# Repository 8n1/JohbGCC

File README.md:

# JohbGCC v1.3

This board is based on the PhobGCC v1.2.3 board (https://github.com/PhobGCC/PhobGCC-HW).  
  
It is 100% compatible with the PhobGCC software but requires a custom teensy.h. (More info below).  

--- 
  
The Board was made with KiCad version 6.0.5.  
Gerber and assembly production files were created using the KiCad plugin "JLCPCB Tools"  (https://github.com/Bouni/kicad-jlcpcb-tools).  

# Changes

- **Rotated the stickbox into original position**  
- **Rotated the Teensy 180°**  
- **Optimized the board paneling for manufacturing**  
- **Added some labels to make it very fail proof and easier to build**  
- **Tried to make the board easier to desolder (More info below)**  

## Other changes 

- **Both hall sensors on the c stick have a decoupling capacitor now**  
- **Routed the 3.3V and filled the top layer with GND too**   

# PCB

# Schematic / PCB tracks

# Custom teensy.h
  
Before uploading the PhobGCC software to the Teensy you need to copy the teensy.h for this board ("Johb1_3Teensy4_0.h") into the "teensy" folder that comes with the Phob software and tell it to use it.   
  
The *teensy.h"* is the configuration file that tells the Phob software to what pins the buttons, triggers, hall sensors are connected to the Teensy.  
  
This board requires a custom one because I re-routed most of the board after rotating the Teensy and to keep tracks nice and short I switched the GPIO pins.  

## Adding the JohbGCC teensy.h 

**Step by step:**
1.  Download the PhobGCC software (https://github.com/PhobGCC/PhobGCC-SW/releases)
2.  Download the JohbGCC teensy.h (https://github.com/8n1/JohbGCC/blob/master/Johb1_3Teensy4_0.h) and put it into the "teensy" folder that is included in the PhobGCC software zip file.
3.  Edit the file "common/phobGCC.h" to use the added JohbGCC teensy.h by adding this line as shown in the picture below:  
```
#include "../teensy/Johb1_3Teensy4_0.h"             // For JohbGCC board 1.3.x with Teensy 4.0
```

4.  Done. Upload it to the Teensy. 

This has been tested with PhobGCC software v0.27 (https://github.com/PhobGCC/PhobGCC-SW/releases/tag/v0.27).  
For earlier versions the steps were slightly different.  
   
This is the only thing necessary to use the JohbGCC board with the PhobGCC software.  

# Modified/cut rumble bracket

It is necessary to modify the rumble bracket because the pins of the hall sensor interfere with it.  
  
**THIS MUST BE DONE, otherwise the controller can't be closed without force which causes various issues because the hall sensor pins will get crushed.**  

The text I put there says that it would be also possible to make the hall sensor pins flat instead but I found it much easier to just cut out a small part of the rumble bracket like shown in the pictures below so I would always recommend doing that.   
   
**"L" rumble bracket:**  
  
**Rumble bracket with integrated trigger guards:**  
  
More pictures before and after cutting:  
https://imgur.com/a/gytP62m  

# Making it easier to desolder

I wanted to make the holes for some parts like the L/R potentiometer and GCC cable not through hole plated to make it easier to desolder (as it is on a OEM GCC board) but I haven't looked into how to do this enough and misunderstood a option in KiCad ("connected layers only") so I didn't got exactly what I wanted:  

But that's not bad actually, part success!  
They are still through hole plated, what that option did was to only remove the solder ring on the side where it's not needed.

... 

After doing some research it looks like that KiCad doesn't has this exact option built in.   
But what you can do is take a smd pad and put a not trough hole plated hole (aka. mounting hole) in the middle of it. But this way this manufacturer specification limitation comes into play (this is from jlcpcb):  

(I want to try this out with the mounting pins of the potentiometers on the next board I make.)

# Pictures

**Hall sensor footprints on c stick**   

**Square indicators that show where the part/cable goes**   

**Labels that indicate hall sensor orientation**   

## More pictures

**Board as it came from JLCPCB:**  
https://imgur.com/a/ONnHoDy

**Soldered board:**  
https://imgur.com/a/rvYWUjU

***

# This project is based on PhobGCC
More informations about the PhobGCC project can be found here:  
https://github.com/PhobGCC  

***

# License
Text and images are licensed under Creative Commons CC-BY-SA.  
[Creative Commons Attribution-ShareAlike 4.0 International License](http://creativecommons.org/licenses/by-sa/4.0/ "Creative Commons Attribution-ShareAlike 4.0 International")  

KiCad board files are licensed under the CERN Open Hardware License.   
[CERN Open Hardware Licence Version 2 - Strongly Reciprocal](https://spdx.org/licenses/CERN-OHL-S-2.0.html "CERN Open Hardware Licence Version 2 - Strongly Reciprocal")  

***

If you have any questions contact me on discord (add me as a friend or find me in the PhobGCC discord): johgi#5103 (Might take a day or two to respond!)

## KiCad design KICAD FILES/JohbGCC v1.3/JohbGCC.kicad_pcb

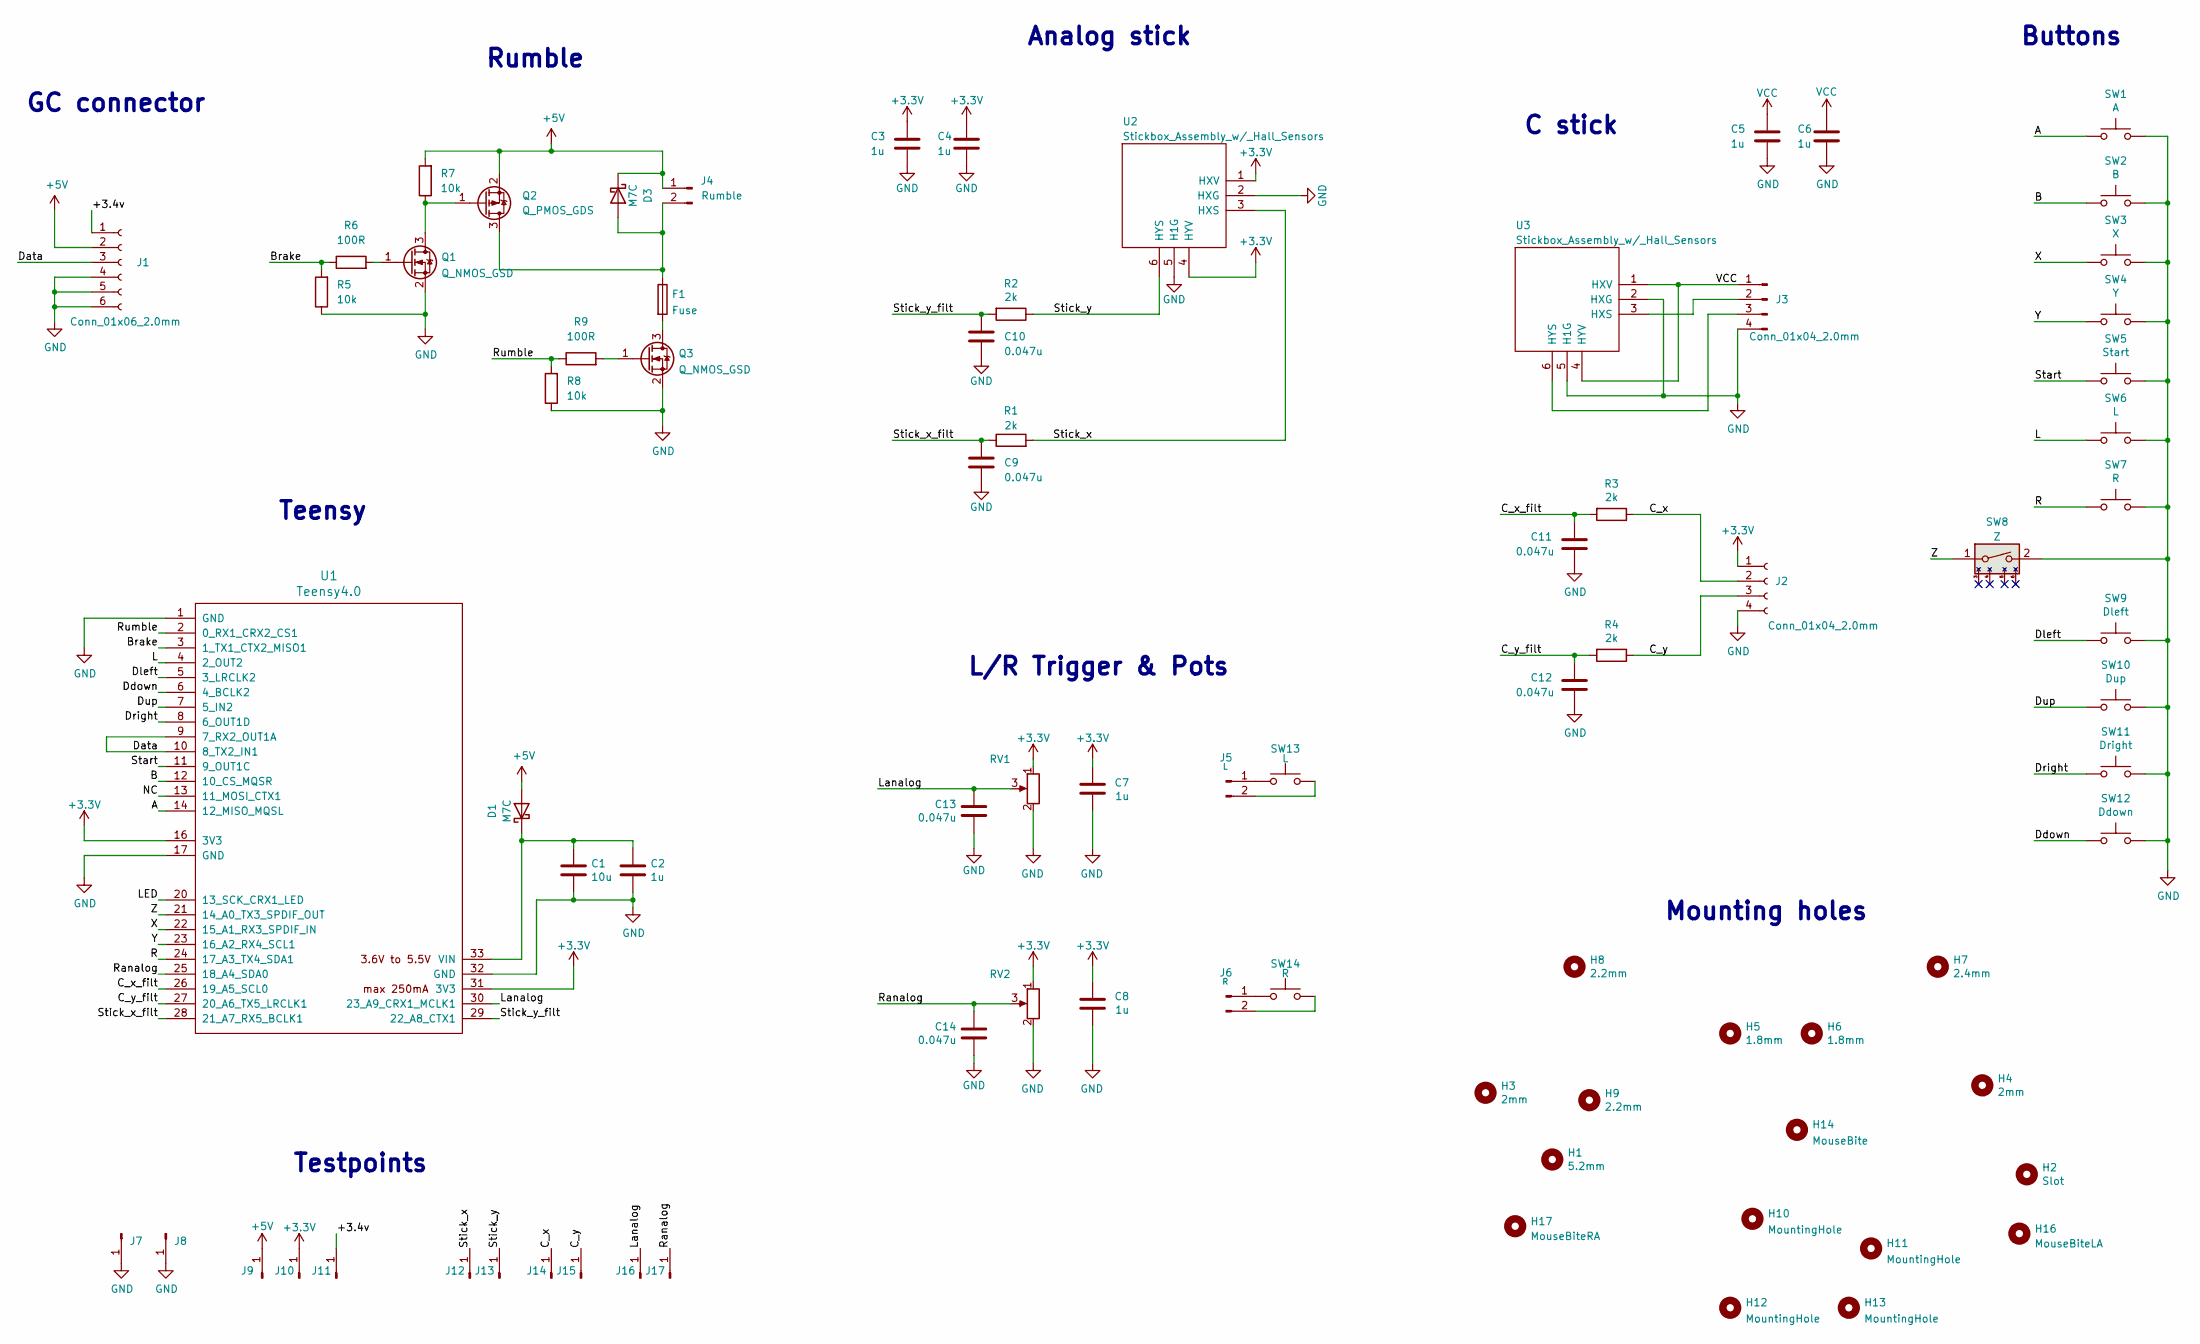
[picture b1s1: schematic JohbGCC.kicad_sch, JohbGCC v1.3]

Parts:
C1: 10u; C_0603_1608Metric_Pad1.08x0.95mm_HandSolder; LCSC C19702
C2, C3, C4, C5, C6, C7, C8: 1u; C_0603_1608Metric_Pad1.08x0.95mm_HandSolder; LCSC C15849
C9, C10, C11, C12, C13, C14: 0.047u; C_0603_1608Metric_Pad1.08x0.95mm_HandSolder; LCSC C1622
D1, D3: M7C; D_SOD-123; LCSC C8598
F1: Fuse; Fuse_1206_3216Metric; LCSC C69680
H1: 5.2mm; MountingHole_5.2mm
H2: Slot
H3, H4: 2mm; MountingHole_2.0mm
H5, H6: 1.8mm; MountingHole_1.8mm
H7: 2.4mm; MountingHole_2.4mm
H8, H9: 2.2mm; MountingHole_2.2mm
H10: MountingHole; MountingHole_1.8mm
H11: MountingHole; MountingHole_5.2mm
H12, H13: MountingHole; MountingHole_2.0mm
H14: MouseBite; JohbGCC_breakaway-mousebites-cstick
H16: MouseBiteLA; JohbGCC_breakaway-mousebites-lr
H17: MouseBiteRA; JohbGCC_breakaway-mousebites-lr
J1: Conn_01x06_2.0mm; GCC_Header_Straight_1x06_Pitch2.00mm
J2, J3: Conn_01x04_2.0mm; PinHeader_1x04_P2.00mm_Vertical
J4: Rumble; rumble_pins
J5: L; Pin_Header_Straight_1x02_Pitch2.54mm
J6: R; Pin_Header_Straight_1x02_Pitch2.54mm
J7, J8, J9, J10, J11, J12, J13, J14, J15, J16, J17: Conn_01x01_Male; PinHeader_1x01_P2.54mm_Vertical
Q1, Q3: Q_NMOS_GSD; SOT-23; LCSC C20917
Q2: Q_PMOS_GDS; SOT-23; LCSC C15127
R1: 2k; R_0603_1608Metric_Pad0.98x0.95mm_HandSolder; Manufacturer PN 0603WAF1002T5ECopy; LCSC C22975
R2, R3, R4: 2k; R_0603_1608Metric_Pad0.98x0.95mm_HandSolder; LCSC C22975
R5, R7, R8: 10k; R_0603_1608Metric_Pad0.98x0.95mm_HandSolder; LCSC C25804
R6, R9: 100R; R_0603_1608Metric_Pad0.98x0.95mm_HandSolder; LCSC C22775
RV1, RV2: R_POT_MountingPin; GCC_Slider
SW1: A; ABXY_Contact_Omron_Switch
SW2: B; ABXY_Contact_Omron_Switch
SW3: X; ABXY_Contact_Omron_Switch
SW4: Y; ABXY_Contact_Omron_Switch
SW5: Start; Start_Contact
SW6: L; Pin_Header_Straight_1x02_Pitch2.54mm
SW7: R; Pin_Header_Straight_1x02_Pitch2.54mm
SW8: Z; Z_Switch_Edge_Omron
SW9: Dleft; Dpad_Contact_TL3315NF_2
SW10: Dup; Dpad_Contact_TL3315NF_2
SW11: Dright; Dpad_Contact_TL3315NF_2
SW12: Ddown; Dpad_Contact_TL3315NF_2
SW13: L; Trigger_Contact
SW14: R; Trigger_Contact
U1: Teensy4.0; Teensy40_Edge_Pins
U2: Stickbox_Assembly_w/_Hall_Sensors; JohbGCC_Stickbox_w_Hall_Sensors_A_Stick
U3: Stickbox_Assembly_w/_Hall_Sensors; JohbGCC_Stickbox_w_Hall_Sensors_C_Stick

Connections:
+3.3V: C3.1, C4.1, C7.1, C8.1, J2.1, J10.1, RV1.1 (V+), RV2.1 (V+), U1.16 (3V3), U1.31 (3V3), U2.1 (HXV), U2.4 (HYV)
+5V: D1.2 (A), D3.1 (K), J1.2, J4.1, J9.1, Q2.2 (S), R7.2
/+3.4v: J1.1, J11.1
/A: SW1.1, U1.14 (12_MISO_MQSL)
/B: SW2.1, U1.12 (10_CS_MQSR)
/Brake: R5.2, R6.1, U1.3 (1_TX1_CTX2_MISO1)
/C_x: J2.2, J14.1, R3.1
/C_x_filt: C11.1, R3.2, U1.26 (19_A5_SCL0)
/C_y: J2.3, J15.1, R4.1
/C_y_filt: C12.1, R4.2, U1.27 (20_A6_TX5_LRCLK1)
/Data: J1.3, U1.9 (7_RX2_OUT1A), U1.10 (8_TX2_IN1)
/Ddown: SW12.1, U1.6 (4_BCLK2)
/Dleft: SW9.1, U1.5 (3_LRCLK2)
/Dright: SW11.1, U1.8 (6_OUT1D)
/Dup: SW10.1, U1.7 (5_IN2)
/L: SW6.1, U1.4 (2_OUT2)
/LED: U1.20 (13_SCK_CRX1_LED)
/Lanalog: C13.1, J16.1, RV1.3 (Signal), U1.30 (23_A9_CRX1_MCLK1)
/NC: U1.13 (11_MOSI_CTX1)
/R: SW7.1, U1.24 (17_A3_TX4_SDA1)
/Ranalog: C14.1, J17.1, RV2.3 (Signal), U1.25 (18_A4_SDA0)
/Rumble: R8.2, R9.1, U1.2 (0_RX1_CRX2_CS1)
/Start: SW5.1, U1.11 (9_OUT1C)
/Stick_x: J12.1, R1.2, U2.3 (HXS)
/Stick_x_filt: C9.1, R1.1, U1.28 (21_A7_RX5_BCLK1)
/Stick_y: J13.1, R2.1, U2.6 (HYS)
/Stick_y_filt: C10.1, R2.2, U1.29 (22_A8_CTX1)
/X: SW3.1, U1.22 (15_A1_RX3_SPDIF_IN)
/Y: SW4.1, U1.23 (16_A2_RX4_SCL1)
/Z: SW8.1, U1.21 (14_A0_TX3_SPDIF_OUT)
GND: C1.2, C2.2, C3.2, C4.2, C5.2, C6.2, C7.2, C8.2, C9.2, C10.2, C11.2, C12.2, C13.2, C14.2, J1.4, J1.5, J1.6, J2.4, J3.4, J7.1, J8.1, Q1.2 (S), Q3.2 (S), R5.1, R8.1, RV1.2 (GND), RV2.2 (GND), SW1.2, SW2.2, SW3.2, SW4.2, SW5.2, SW6.2, SW7.2, SW8.2, SW9.2, SW10.2, SW11.2, SW12.2, U1.1 (GND), U1.17 (GND), U1.32 (GND), U2.2 (HXG), U2.5 (H1G), U3.2 (HXG), U3.5 (H1G)
unnamed: C1.1, C2.1, D1.1 (K), U1.33 (VIN)
unnamed: D3.2 (A), F1.1, J4.2, Q2.3 (D)
unnamed: F1.2, Q3.3 (D)
unnamed: J3.2, U3.3 (HXS)
unnamed: J3.3, U3.6 (HYS)
unnamed: J5.1, SW13.2
unnamed: J5.2, SW13.1
unnamed: J6.1, SW14.2
unnamed: J6.2, SW14.1
unnamed: Q1.1 (G), R6.2
unnamed: Q1.3 (D), Q2.1 (G), R7.1
unnamed: Q3.1 (G), R9.2
VCC: C5.1, C6.1, J3.1, U3.1 (HXV), U3.4 (HYV)

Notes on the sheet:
Buttons
Rumble
C stick
Analog stick
Testpoints
L/R Trigger & Pots
GC connector
Teensy
Mounting holes

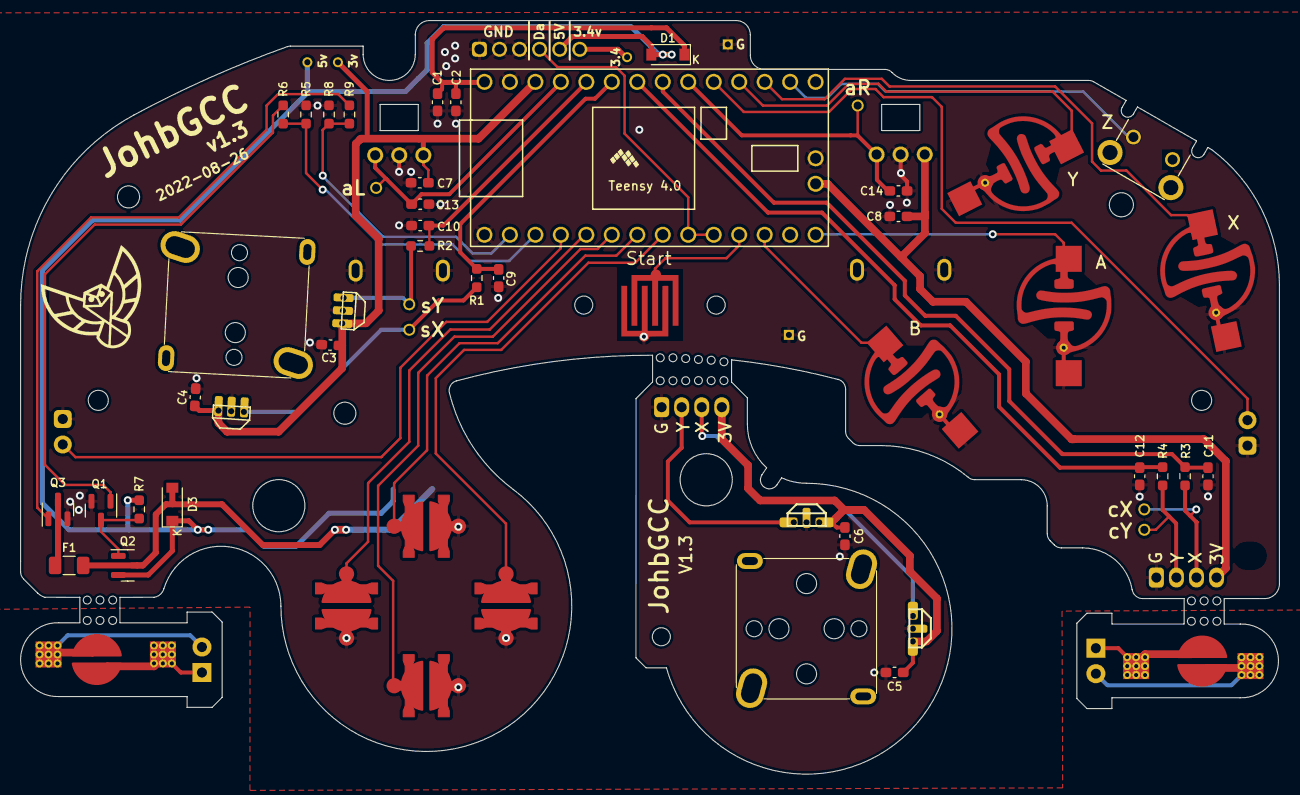
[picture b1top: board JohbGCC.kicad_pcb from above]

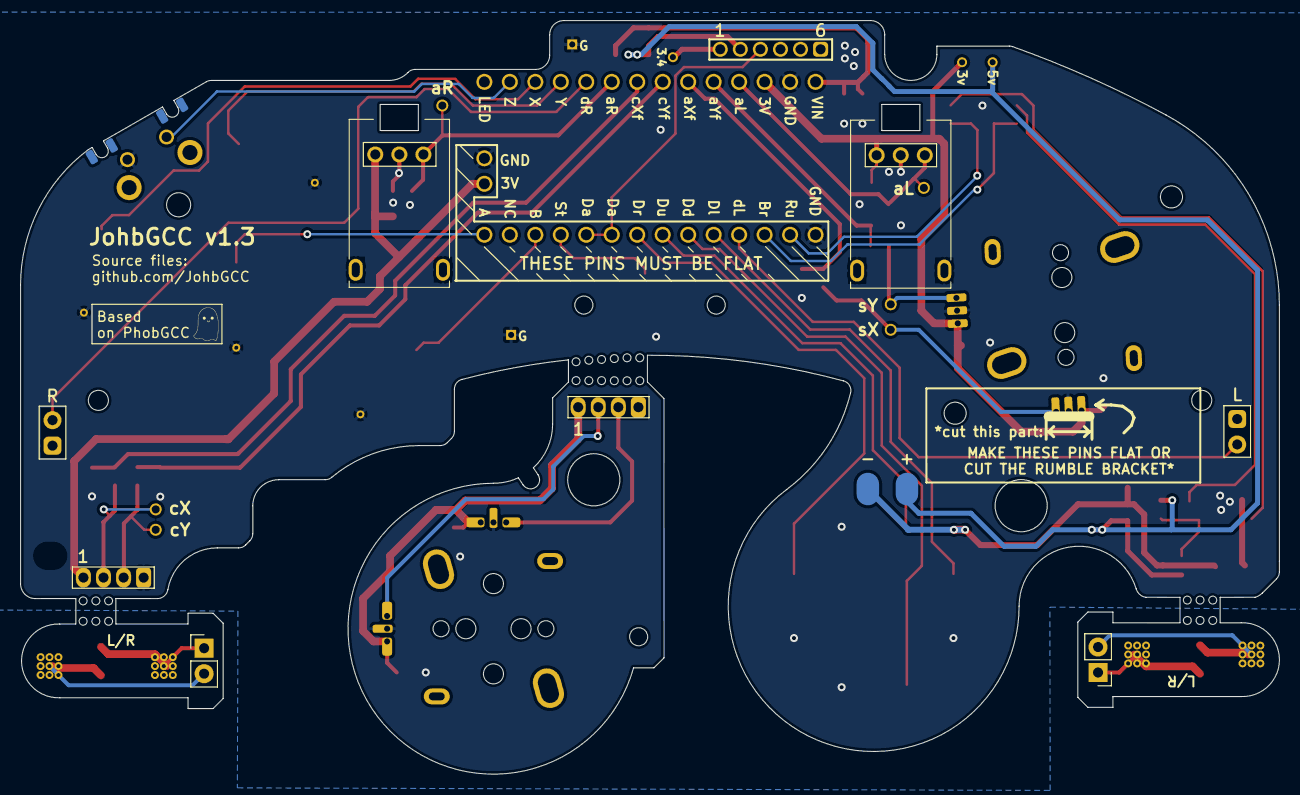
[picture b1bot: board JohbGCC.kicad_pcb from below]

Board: 2 copper layers, 125.5 x 75.1 mm, 81 parts (20 on the bottom side), 42 nets.

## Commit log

2022-10-19 initial upload
2022-10-19 fixed link to the johb teensy.h
